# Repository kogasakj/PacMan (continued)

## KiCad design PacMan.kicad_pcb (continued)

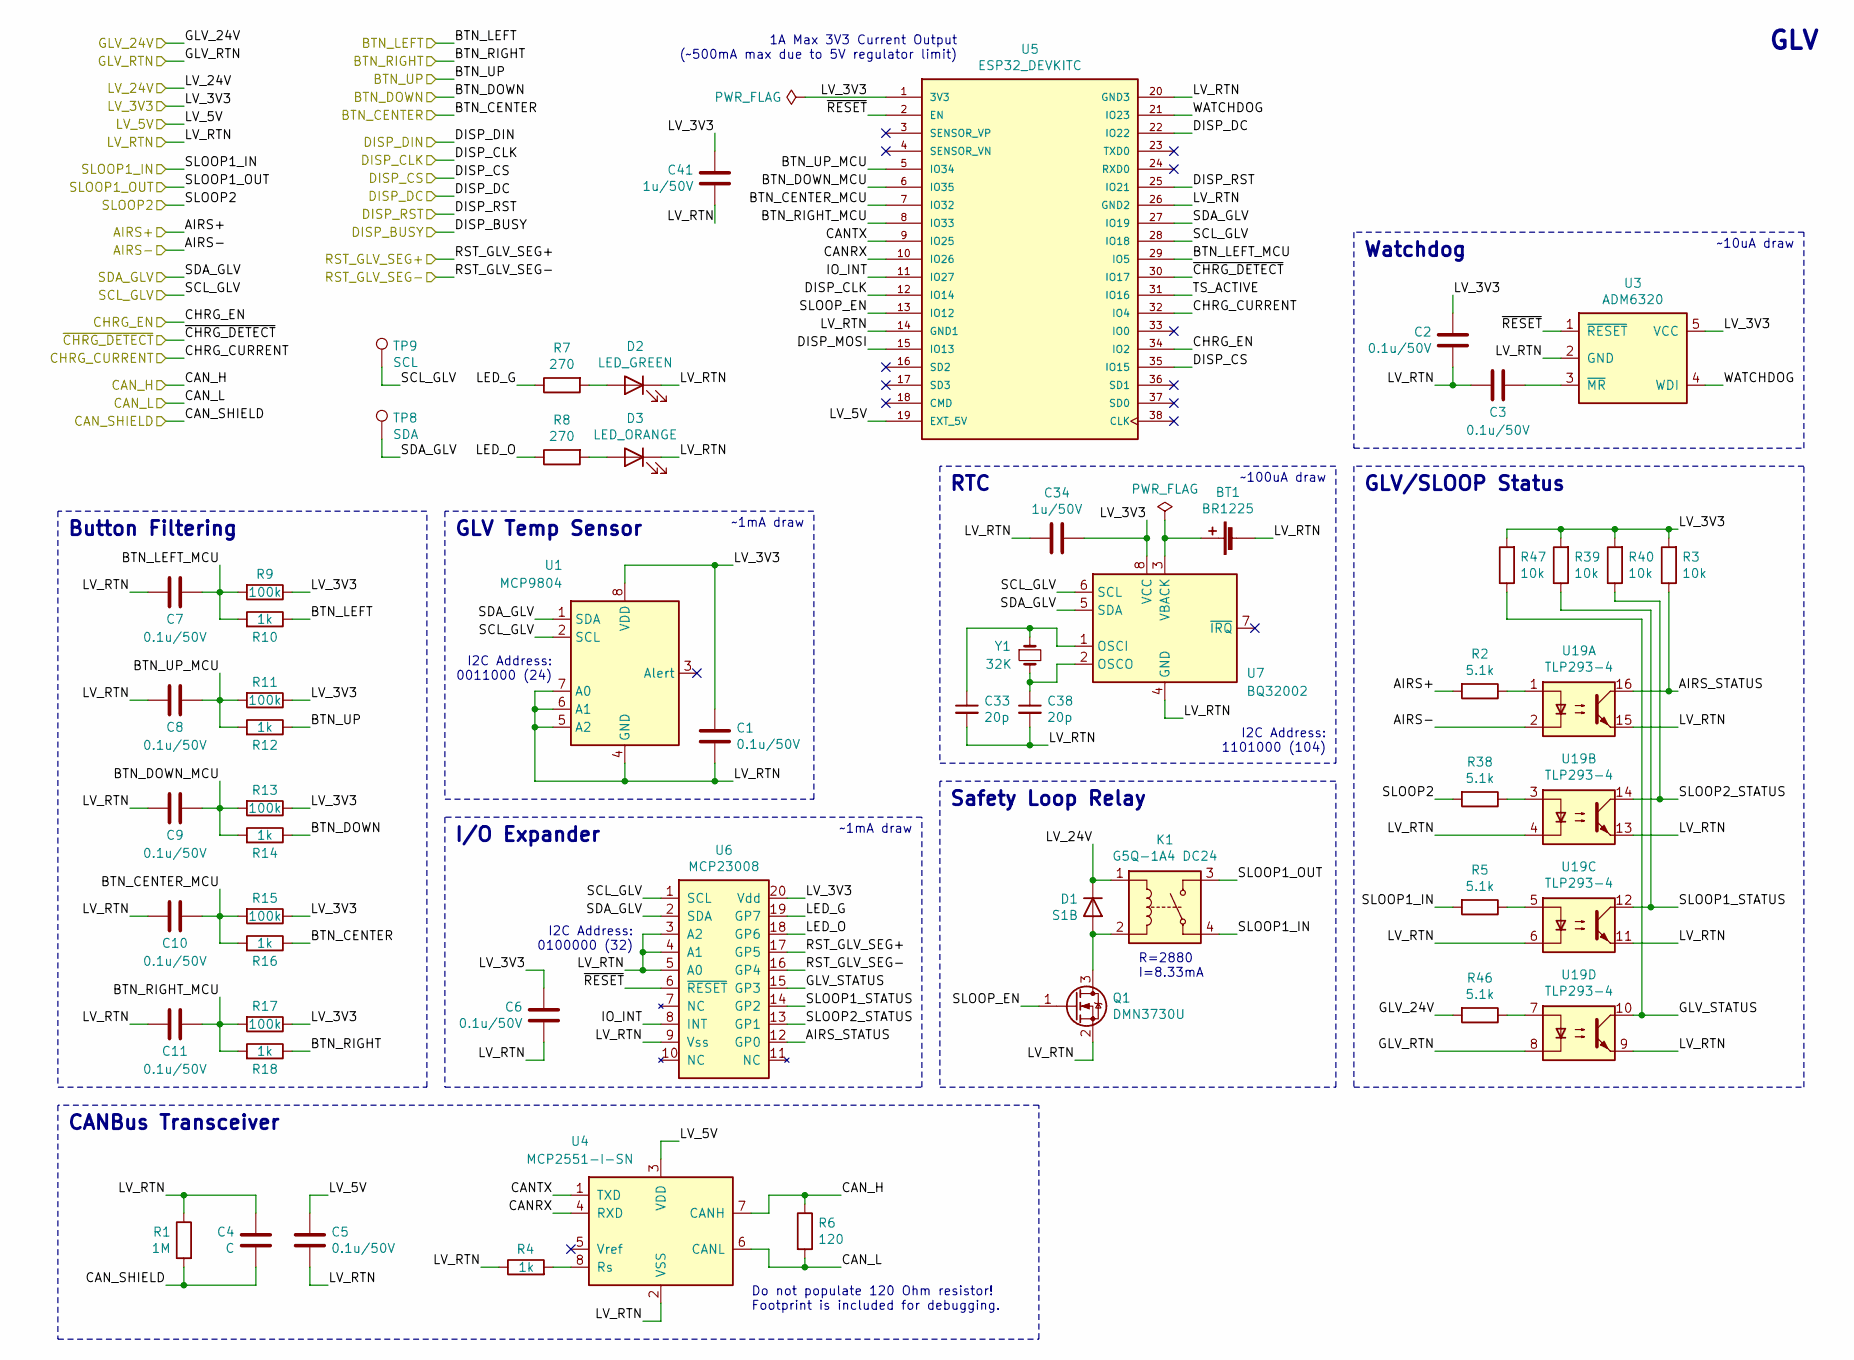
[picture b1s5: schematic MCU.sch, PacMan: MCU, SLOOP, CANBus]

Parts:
BT1: BR1225; BatteryHolder_Keystone_103_1x20mm; Manufacturer Part BR-1225
C1, C2, C3, C5, C6, C7, C8, C9, C10, C11: 0.1u/50V; C_0805_2012Metric_Pad1.15x1.40mm_HandSolder; Manufacturer Part CL21B104KBCNNNC
C4: C; C_0805_2012Metric_Pad1.15x1.40mm_HandSolder
C33, C38: 20p; C_0805_2012Metric_Pad1.15x1.40mm_HandSolder; Manufacturer Part CL21C200JBANNNC
C34, C41: 1u/50V; C_0805_2012Metric_Pad1.15x1.40mm_HandSolder; Manufacturer Part CL21B105KBFNNNG
D1: S1B; D_SMA_Handsoldering; Manufacturer Part S1B-13-F
D2: LED_GREEN; LED_0805_2012Metric_Pad1.15x1.40mm_HandSolder; Manufacturer Part LTST-C170GKT
D3: LED_ORANGE; LED_0805_2012Metric_Pad1.15x1.40mm_HandSolder; Manufacturer Part LTST-C171AKT
K1: G5Q-1A4 DC24; G5Q-1A4; Manufacturer Part G5Q-1A4 DC24
Q1: DMN3730U; SOT-23; Manufacturer Part DMN3730U-7
R1: 1M; R_0805_2012Metric_Pad1.15x1.40mm_HandSolder
R2, R5, R38, R46: 5.1k; R_0805_2012Metric_Pad1.15x1.40mm_HandSolder
R3, R39, R40, R47: 10k; R_0805_2012Metric_Pad1.15x1.40mm_HandSolder
R4, R10, R12, R14, R16, R18: 1k; R_0805_2012Metric_Pad1.15x1.40mm_HandSolder
R6: 120; R_0805_2012Metric_Pad1.15x1.40mm_HandSolder
R7, R8: 270; R_0805_2012Metric_Pad1.15x1.40mm_HandSolder
R9, R11, R13, R15, R17: 100k; R_0805_2012Metric_Pad1.15x1.40mm_HandSolder
TP8: SDA; TestPoint_Pad_D1.5mm
TP9: SCL; TestPoint_Pad_D1.5mm
U1: MCP9804; MSOP-8_3x3mm_P0.65mm; Manufacturer Part MCP9804T-E/MS
U3: ADM6320; SOT-23-5; Manufacturer Part ADM6320CY29ARJZ-R7
U4: MCP2551-I-SN; SOIC-8_3.9x4.9mm_P1.27mm; Manufacturer Part MCP2551T-I/SN
U5: ESP32_DEVKITC; MODULE_ESP32-DEVKITC-32D; Manufacturer Part ESP32-DEVKITC-32D
U6: MCP23008; SSOP-20_5.3x7.2mm_P0.65mm; Manufacturer Part MCP23008T-E/SS
U7: BQ32002; SOIC-8_3.9x4.9mm_P1.27mm; Manufacturer Part BQ32002DR
U19: TLP293-4; SOIC-16_4.55x10.3mm_P1.27mm; Manufacturer Part TLP293-4
Y1: 32K; Crystal_SMD_SeikoEpson_MC405-2Pin_9.6x4.1mm; Manufacturer Part MC-405 32.7680K-A0:ROHS

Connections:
/AIRS+: R2.2; also elsewhere on the board
/AIRS-: U19.2; also elsewhere on the board
/BTN_CENTER: R16.1; also elsewhere on the board
/BTN_DOWN: R14.1; also elsewhere on the board
/BTN_LEFT: R10.1; also elsewhere on the board
/BTN_RIGHT: R18.1; also elsewhere on the board
/BTN_UP: R12.1; also elsewhere on the board
/CAN_H: R6.1, U4.7 (CANH); also elsewhere on the board
/CAN_L: R6.2, U4.6 (CANL); also elsewhere on the board
/CAN_SHIELD: C4.2, R1.2; also elsewhere on the board
/CHRG_CURRENT: U5.32 (IO4); also elsewhere on the board
/CHRG_EN: U5.34 (IO2); also elsewhere on the board
/DISP_CLK: U5.12 (IO14); also elsewhere on the board
/DISP_CS: U5.35 (IO15); also elsewhere on the board
/DISP_DC: U5.22 (IO22); also elsewhere on the board
/DISP_RST: U5.25 (IO21); also elsewhere on the board
/GLV_24V: R46.2; also elsewhere on the board
/GLV_RTN: BT1.2 (-), C1.2, C2.2, C3.2, C4.1, C5.2, C6.2, C7.2, C8.2, C9.2, C10.2, C11.2, C33.2, C34.2, C38.2, C41.2, D2.1 (K), D3.1 (K), Q1.2 (S), R1.1, R4.1, U1.4 (GND), U1.5 (A2), U1.6 (A1), U1.7 (A0), U3.2 (GND), U4.2 (VSS), U5.14 (GND1), U5.20 (GND3), U5.26 (GND2), U6.3 (A2), U6.4 (A1), U6.5 (A0), U6.9 (Vss), U7.4 (GND), U19.4, U19.6, U19.8, U19.9, U19.11, U19.13, U19.15; also elsewhere on the board
/LV_3V3: C1.1, C2.1, C6.1, C34.1, C41.1, R3.2, R9.1, R11.1, R13.1, R15.1, R17.1, R39.2, R40.2, R47.2, U1.8 (VDD), U3.5 (VCC), U5.1 (3V3), U6.20 (Vdd), U7.8 (VCC); also elsewhere on the board
/LV_5V: C5.1, U4.3 (VDD), U5.19 (EXT_5V); also elsewhere on the board
/LV_24V: D1.1 (K), K1.1; also elsewhere on the board
/MCU/AIRS_STATUS: R3.1, U6.12 (GP0), U19.16
/MCU/BTN_CENTER_MCU: C10.1, R15.2, R16.2, U5.7 (IO32)
/MCU/BTN_DOWN_MCU: C9.1, R13.2, R14.2, U5.6 (IO35)
/MCU/BTN_LEFT_MCU: C7.1, R9.2, R10.2, U5.29 (IO5)
/MCU/BTN_RIGHT_MCU: C11.1, R17.2, R18.2, U5.8 (IO33)
/MCU/BTN_UP_MCU: C8.1, R11.2, R12.2, U5.5 (IO34)
/MCU/CANRX: U4.4 (RXD), U5.10 (IO26)
/MCU/CANTX: U4.1 (TXD), U5.9 (IO25)
/MCU/DISP_MOSI: U5.15 (IO13)
/MCU/GLV_STATUS: R47.1, U6.15 (GP3), U19.10
/MCU/IO_INT: U5.11 (IO27), U6.8 (INT)
/MCU/LED_G: R7.1, U6.19 (GP7)
/MCU/LED_O: R8.1, U6.18 (GP6)
/MCU/SLOOP1_STATUS: R39.1, U6.14 (GP2), U19.12
/MCU/SLOOP2_STATUS: R40.1, U6.13 (GP1), U19.14
/MCU/SLOOP_EN: Q1.1 (G), U5.13 (IO12)
/MCU/TS_ACTIVE: U5.31 (IO16)
/MCU/WATCHDOG: U3.4 (WDI), U5.21 (IO23)
/MCU/~RESET: U3.1 (~RESET), U5.2 (EN), U6.6 (~RESET)
/RST_GLV_SEG+: U6.17 (GP5); also elsewhere on the board
/RST_GLV_SEG-: U6.16 (GP4); also elsewhere on the board
/SCL_GLV: TP9.1, U1.2 (SCL), U5.28 (IO18), U6.1 (SCL), U7.6 (SCL); also elsewhere on the board
/SDA_GLV: TP8.1, U1.1 (SDA), U5.27 (IO19), U6.2 (SDA), U7.5 (SDA); also elsewhere on the board
/SLOOP1_IN: K1.4, R5.2; also elsewhere on the board
/SLOOP1_OUT: K1.3; also elsewhere on the board
/SLOOP2: R38.2; also elsewhere on the board
/~CHRG_DETECT: U5.30 (IO17); also elsewhere on the board
unnamed: BT1.1 (+), U7.3 (VBACK)
unnamed: C3.1, U3.3 (~MR)
unnamed: C33.1, U7.1 (OSCI), Y1.1
unnamed: C38.1, U7.2 (OSCO), Y1.2
unnamed: D1.2 (A), K1.2, Q1.3 (D)
unnamed: D2.2 (A), R7.2
unnamed: D3.2 (A), R8.2
unnamed: R2.1, U19.1
unnamed: R4.2, U4.8 (Rs)
unnamed: R5.1, U19.5
unnamed: R38.1, U19.3
unnamed: R46.1, U19.7

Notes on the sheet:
Do not populate 120 Ohm resistor! Footprint is included for debugging.
GLV
I2C Address: 0100000 (32)
Button Filtering
RTC
CANBus Transceiver
Safety Loop Relay
I/O Expander
I2C Address: 0011000 (24)
GLV Temp Sensor
R=2880 I=8.33mA
GLV/SLOOP Status
~~1mA draw
1A Max 3V3 Current Output (~~500mA max due to 5V regulator limit)
I2C Address: 1101000 (104)
Watchdog
~~100uA draw
~~10uA draw

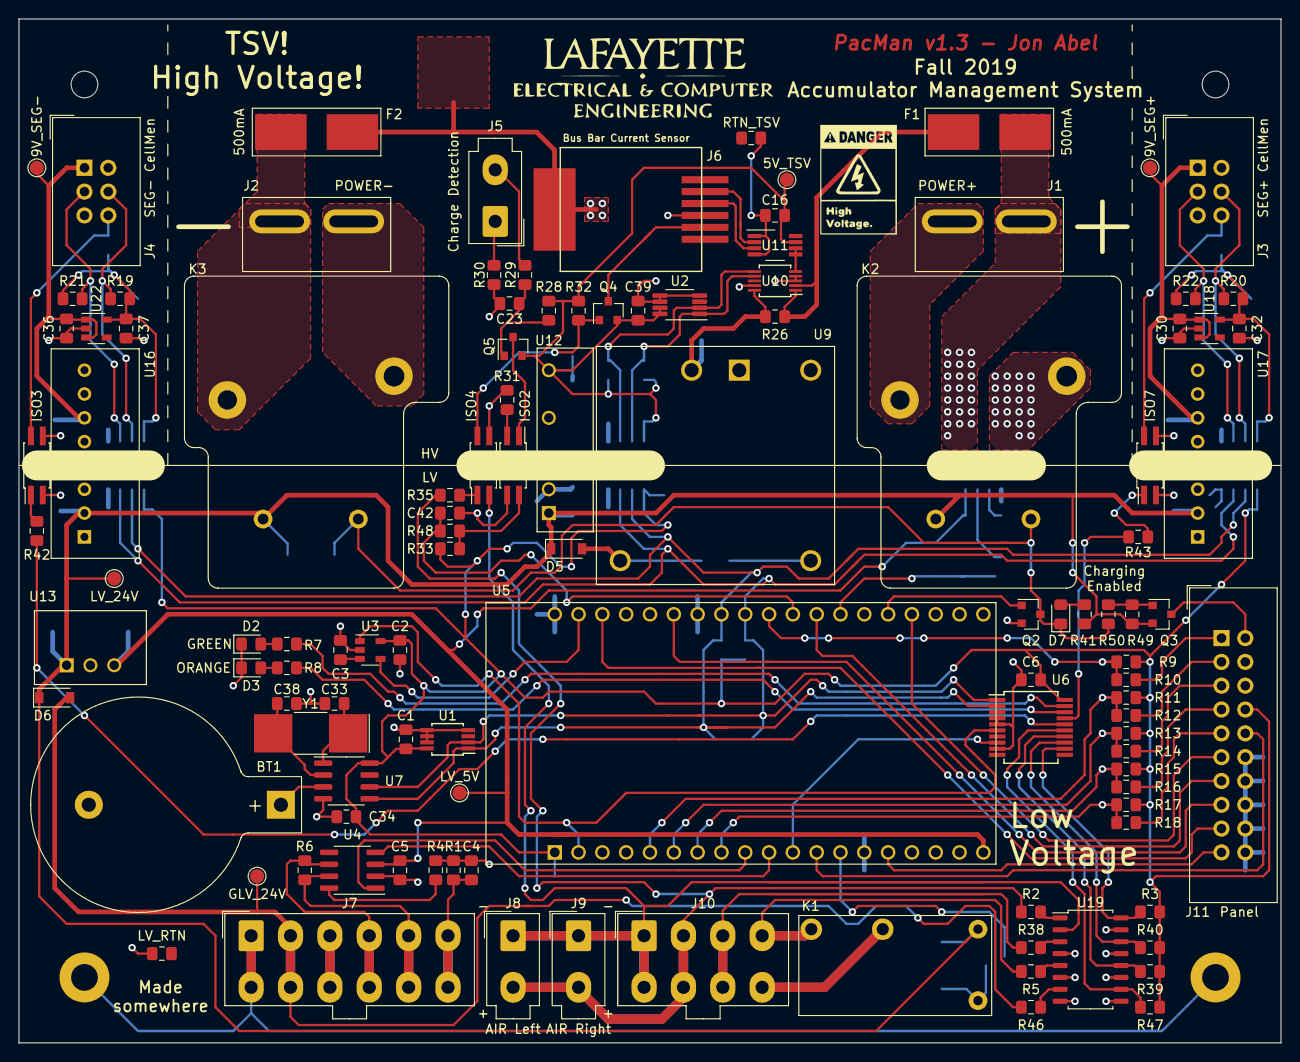
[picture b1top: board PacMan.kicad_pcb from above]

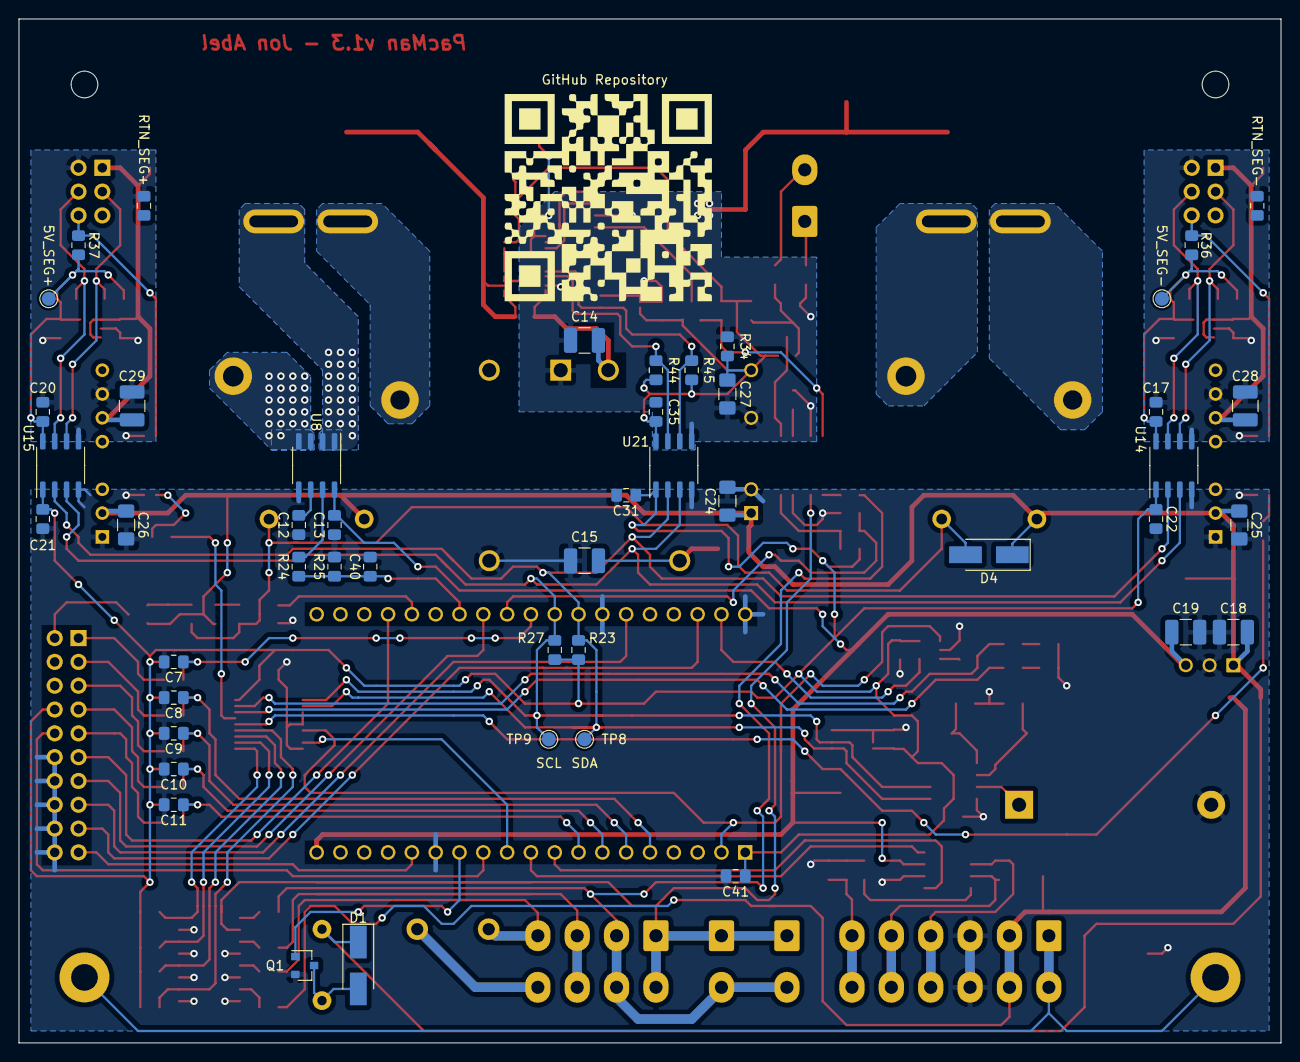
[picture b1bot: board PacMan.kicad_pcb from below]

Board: 2 copper layers, 134.6 x 109.2 mm, 168 parts (47 on the bottom side), 103 nets.
